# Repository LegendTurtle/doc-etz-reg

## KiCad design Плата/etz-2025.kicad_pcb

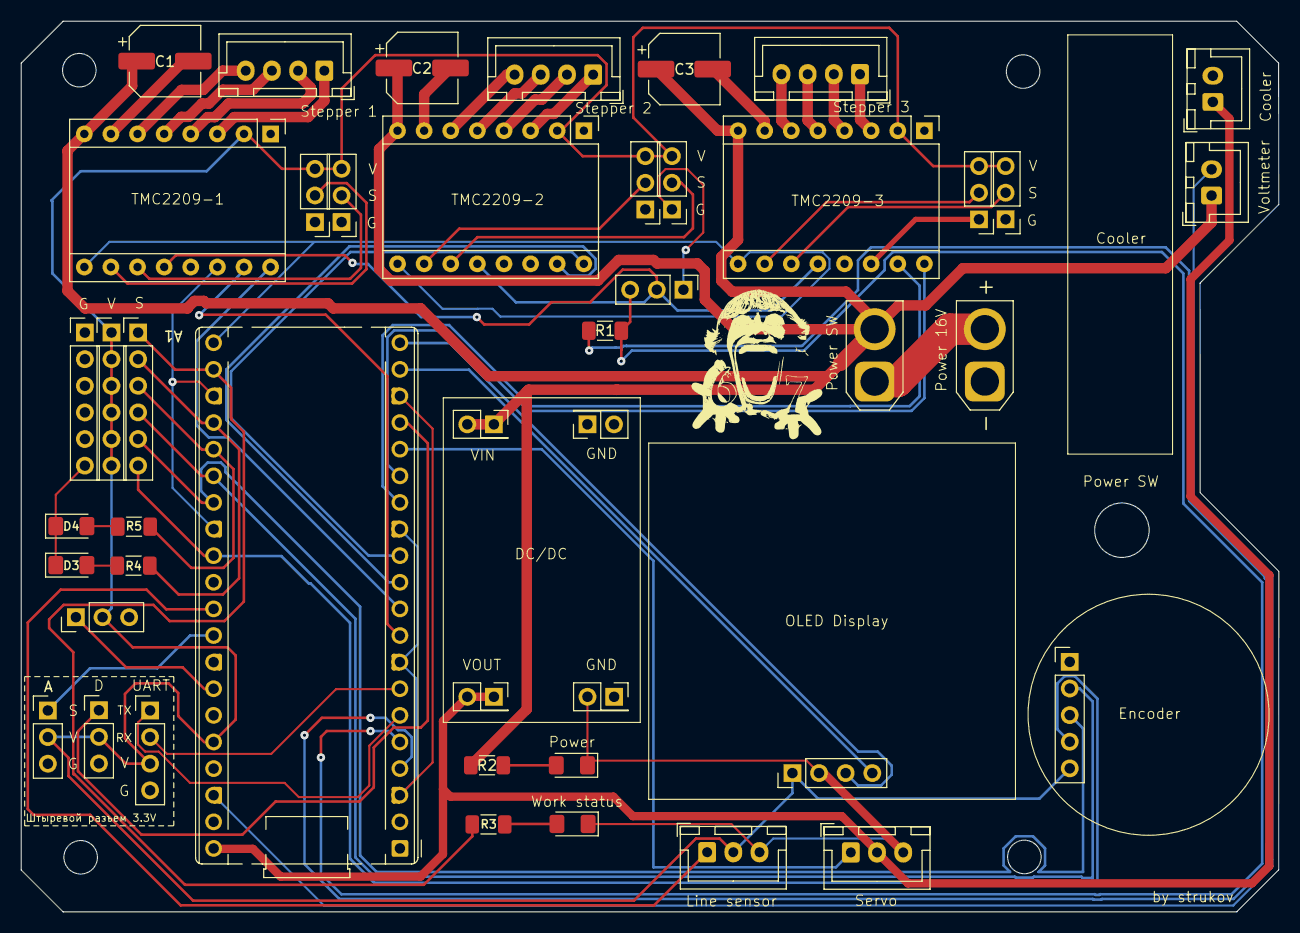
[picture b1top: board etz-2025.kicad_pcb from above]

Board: 2 copper layers, 120.0 x 85.0 mm, 49 parts (0 on the bottom side), 52 nets.

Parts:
A1: RaspberryPi_Pico; RaspberryPi_Pico_Common_THT
A2: TMC2209-1; Pololu_Breakout-16_15.2x20.3mm
A3: TMC2209-2; Pololu_Breakout-16_15.2x20.3mm
A4: TMC2209-3; Pololu_Breakout-16_15.2x20.3mm
C1, C2, C3: 100uF 25V; CP_Elec_6.3x7.7
D1: Power LED; LED_1206_3216Metric_Pad1.42x1.75mm_HandSolder
D2: Status LED; LED_1206_3216Metric_Pad1.42x1.75mm_HandSolder
D3: LED1; LED_1206_3216Metric_Pad1.42x1.75mm_HandSolder
D4: LED2; LED_1206_3216Metric_Pad1.42x1.75mm_HandSolder
H1, H2, H3, H4: Mount hole; MountingHole_3.2mm_M3
J1: Stepper 1 connector; JST_XH_B4B-XH-A_1x04_P2.50mm_Vertical
J2: MS1-1 setup; PinHeader_1x03_P2.54mm_Vertical
J3: MS2-1 setup; PinHeader_1x03_P2.54mm_Vertical
J4: Stepper 2 connector; JST_XH_B4B-XH-A_1x04_P2.50mm_Vertical
J5: MS1-2 setup; PinHeader_1x03_P2.54mm_Vertical
J6: MS2-2 setup; PinHeader_1x03_P2.54mm_Vertical
J7: Stepper 3 connector; JST_XH_B4B-XH-A_1x04_P2.50mm_Vertical
J8: MS1-3 setup; PinHeader_1x03_P2.54mm_Vertical
J9: MS2-3 setup; PinHeader_1x03_P2.54mm_Vertical
J10: XT30; AMASS_XT30U-F_1x02_P5.0mm_Vertical
J11: Servo; JST_XH_B3B-XH-A_1x03_P2.50mm_Vertical
J12: LINE-SENSOR; JST_XH_B3B-XH-A_1x03_P2.50mm_Vertical
J13: Analog connector; PinHeader_1x03_P2.54mm_Vertical
J14: Digital connector; PinHeader_1x03_P2.54mm_Vertical
J15: UART connector; PinHeader_1x04_P2.54mm_Vertical
J16: Encoder connector; PinHeader_1x05_P2.54mm_Vertical
J17: Voltmeter; JST_XH_B2B-XH-A_1x02_P2.50mm_Vertical
J18: OLED I2C connector; PinHeader_1x04_P2.54mm_Vertical
J19: Cooler; JST_XH_B2B-XH-A_1x02_P2.50mm_Vertical
J20: GPIO connector; PinHeader_1x06_P2.54mm_Vertical
J21: DC/DC VIN +; PinSocket_2x01_P2.54mm_Vertical
J22: DC/DC OUT +; PinSocket_2x01_P2.54mm_Vertical
J23: DC/DC VIN -; PinSocket_2x01_P2.54mm_Vertical
J24: DC/DC VOUT -; PinSocket_2x01_P2.54mm_Vertical
J25: GND connector; PinHeader_1x06_P2.54mm_Vertical
J26: 3V3 connector; PinHeader_1x06_P2.54mm_Vertical
J27: Analog connector 2; PinHeader_1x03_P2.54mm_Vertical
J28: UART conn; PinHeader_1x03_P2.54mm_Vertical
R1, R2: 2.2k; R_1206_3216Metric_Pad1.30x1.75mm_HandSolder
R3, R4, R5: R100; R_1206_3216Metric_Pad1.30x1.75mm_HandSolder
SW1: Power SW; AMASS_XT30U-F_1x02_P5.0mm_Vertical

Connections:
3V3: A1.36 (3V3), A2.2 (VDD), A3.2 (VDD), A4.2 (VDD), J2.3, J3.3, J5.3, J6.3, J8.3, J9.3, J12.2, J13.2, J14.2, J15.3, J16.5, J18.1, J26.1, J26.2, J26.3, J26.4, J26.5, J26.6, J27.2
5V: A1.40 (VBUS), J11.2, J19.1, J22.1, J22.2
16V: A2.8 (VMOT), A3.8 (VMOT), A4.8 (VMOT), C1.1, C2.1, C3.1, J17.1, J21.1, J21.2, R2.1, SW1.2
A2: A1.34 (GPIO28_ADC2), J27.1
ANALOG-CONN: A1.32 (GPIO27_ADC1), J13.1
DIG-CONN: A1.17 (GPIO13), J14.1
DIR-1: A1.10 (GPIO7), A2.16 (DIR)
DIR-2: A1.12 (GPIO9), A3.16 (DIR)
DIR-3: A1.15 (GPIO11), A4.16 (DIR)
EN: A1.21 (GPIO16), A2.9 (~ENABLE), A3.9 (~ENABLE), A4.9 (~ENABLE)
GND: A1.3 (GND), A1.8 (GND), A1.13 (GND), A1.18 (GND), A1.23 (GND), A1.28 (GND), A1.38 (GND), A2.1 (GND), A2.7 (GND), A2.14 (~SLEEP), A3.1 (GND), A3.7 (GND), A3.14 (~SLEEP), A4.1 (GND), A4.7 (GND), A4.14 (~SLEEP), C1.2, C2.2, C3.2, D1.1 (K), D2.1 (K), D3.1 (K), D4.1 (K), J2.1, J3.1, J5.1, J6.1, J8.1, J9.1, J10.1, J11.3, J12.3, J13.3, J14.3, J15.4, J16.1, J17.2, J18.2, J19.2, J23.1, J23.2, J24.1, J24.2, J25.1, J25.2, J25.3, J25.4, J25.5, J25.6, J27.3, J28.1
GPIO17: A1.22 (GPIO17), J20.1, R3.1
GPIO18: A1.24 (GPIO18), J20.2, R4.1
GPIO19: A1.25 (GPIO19), J20.3, R5.1
GPIO20: A1.26 (GPIO20), J16.2, J20.4
GPIO21: A1.27 (GPIO21), J16.3, J20.5
GPIO22: A1.29 (GPIO22), J16.4, J20.6
LINE-SENSOR: A1.31 (GPIO26_ADC0), J12.1
M1-1A: A2.4 (1A), J1.2
M1-1B: A2.3 (1B), J1.1
M1-2A: A2.5 (2A), J1.3
M1-2B: A2.6 (2B), J1.4
M2-1A: A3.4 (1A), J4.2
M2-1B: A3.3 (1B), J4.1
M2-2A: A3.5 (2A), J4.3
M2-2B: A3.6 (2B), J4.4
M3-1A: A4.4 (1A), J7.2
M3-1B: A4.3 (1B), J7.1
M3-2A: A4.5 (2A), J7.3
M3-2B: A4.6 (2B), J7.4
MS1-1: A2.10 (MS1), J2.2
MS1-2: A3.10 (MS1), J5.2
MS1-3: A4.10 (MS1), J8.2
MS2-1: A2.11 (MS2), J3.2
MS2-2: A3.11 (MS2), J6.2
MS2-3: A4.11 (MS2), J9.2
unnamed: D1.2 (A), R2.2
unnamed: D2.2 (A), R3.2
unnamed: D3.2 (A), R4.2
unnamed: D4.2 (A), R5.2
PDN: A2.12 (MS3), A3.12 (MS3), A4.12 (MS3), J28.2
SCL: A1.20 (GPIO15), J18.3
SDA: A1.19 (GPIO14), J18.4
SERVO: A1.16 (GPIO12), J11.1
STEP-1: A1.9 (GPIO6), A2.15 (STEP)
STEP-2: A1.11 (GPIO8), A3.15 (STEP)
STEP-3: A1.14 (GPIO10), A4.15 (STEP)
UART1-RX: A1.7 (GPIO5), J15.2
UART1-TX: A1.6 (GPIO4), J15.1
UARTMOT-RX: A1.5 (GPIO3), J28.3, R1.2
UARTMOT-TX: A1.4 (GPIO2), R1.1
VIN: J10.2, SW1.1
